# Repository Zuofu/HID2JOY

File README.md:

# HID2JOY
## Xbox One Controller (and other USB) to Analog IBM PC Gameport Adapter

### Intro
DOSBox has had the ability to map Xbox controllers to "Gameport" for a long time, but as far as I know, this is the first for people who want to use old hardware. I know of many converters that go the other way (use your old peripherals on a modern machine), but this allows you to use your nicer new controller with old machines. Anyway, this is WIP right now, and relies on Arduino, the USB Host Shield (MAX3421E) along with a Microchip DPot (actually, it's a rheostat). For now it only works with the Xbox One controller, since that's what the example code I started with is based off of, though it is trivial to extend to other supported controllers (Dualshock 3/4, Xbox 360..etc).

PCB is here: https://oshpark.com/projects/cPoLc5l8

### BOM:

1x Arduino Pro Mini or equivalent 3.3 V required - official or clones are fine, but make sure it's 3.3V

1x Mini USB Host Shield (based on MAX3421E) - find on eBay/Aliexpress/etc

1x MCP4452-104E digital rheostat (100K, quad channel, I2C)

2x 0603 4.7 kOhm resistor

1x 0603 .1uF ceramic capacitor

2x CES-112-01-T-S 12 position .1" pin header (low profile)

1x CES-102-02-T-S 2 position .1" pin header (low profile) or cut from larger part

1x ID15P33E4GV00LF or equivalent DB15 Male Connector right angle 2 row

Various .1" pin header strips

### Building and Modifications:

You should cut the trace on the USB Host Shield between 3.3V and VUSB, and then wire a jumper from RAW to VUSB. This will allow the controller to work with 5V (as per the USB spec) and also bypass the already overloaded regulator on the Arduino. Otherwise assemble the base PCB, then solder the Mini Host Shield with the Arduino into a stack and then solder the stack to the base PCB. Program the Arduino with the code as follows (you will need some USB serial port). If you get build errors, make sure you've installed the USB Host Shield 2.0 library using the Arduino Library manager. Make sure you connect also connected A6/A7 used for I2C (these are the two connections not in the parallel headers) between the Arduino and the PCB.

### Additional Usage Instructions (subject to change):
Holding down VIEW for 3 seconds switches modes. Here are the currently supported modes:

Standard 4 axis 4 button (mode 1)
Triggers and Buttons overloaded to A/B/X/Y

Thrustmaster emulation (mode 2)
Triggers are used for analog rudder X2 (Left/Right relative). Y2 is used for POV hat, multiple simultanous button presses are allowed. Note, I don't know the correct resistance values, can someone who owns Thrustmaster measure?

CH Flightstick emulation (mode 3)
Triggers are used for analog rudder X2 (Left/Right relative), left stick is used for digital POV hat along with D-pad. Buttons chords are used for POV hat (digital) . Multiple simultanous button pressed not allowed.

CH Flightstick emulation alternate (mode 4)
Triggers are used for analog rudder X2 (Left/Right relative), left stick is used for throttle (up/down). Buttons chords are used for POV hat (digital) with D-pad. Multiple simultanous button pressed not allowed.

Current design remembers last mode using EEPROM and will power up with last used mode.

Holding down MENU for 3 seconds swaps behavior of left and right sticks.

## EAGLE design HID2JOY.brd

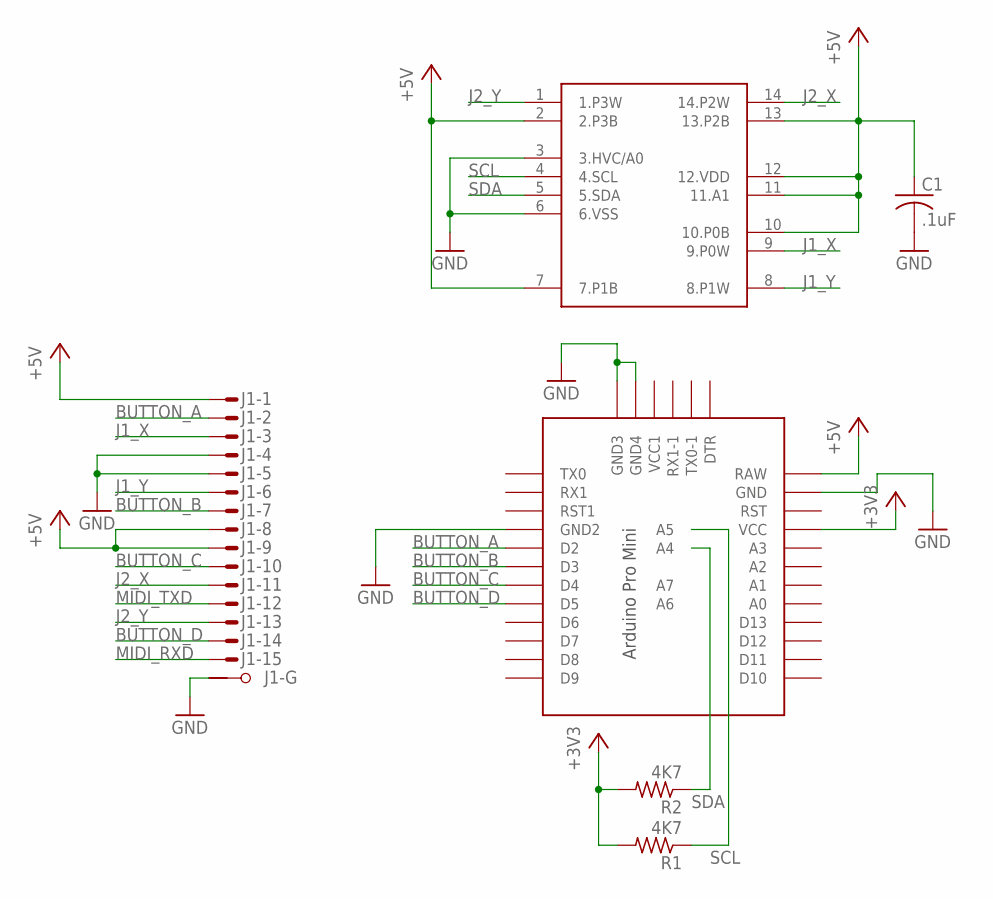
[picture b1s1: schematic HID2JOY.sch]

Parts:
C1: .1uF; C0603
J1: M15HPS; M15HP
R1, R2: 4K7; R0603
U1: PCM44X2TSSOP; TSSOP14
U$1: PRO-MINI-2

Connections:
+3V3: R1.2, R2.2, U$1.VCC
+5V: C1.1, J1.1 (M), J1.8 (M), J1.9 (M), U1.2 (2.P3B), U1.7 (7.P1B), U1.10 (10.P0B), U1.11 (11.A1), U1.12 (12.VDD), U1.13 (13.P2B), U$1.RAW
BUTTON_A: J1.2 (M), U$1.D2
BUTTON_B: J1.7 (M), U$1.D3
BUTTON_C: J1.10 (M), U$1.D4
BUTTON_D: J1.14 (M), U$1.D5
GND: C1.2, J1.4 (M), J1.5 (M), J1.G1, U1.3 (3.HVC/A0), U1.6 (6.VSS), U$1.GND, U$1.GND1 (GND2), U$1.GND2 (GND3), U$1.GND3 (GND4)
J1_X: J1.3 (M), U1.9 (9.P0W)
J1_Y: J1.6 (M), U1.8 (8.P1W)
J2_X: J1.11 (M), U1.14 (14.P2W)
J2_Y: J1.13 (M), U1.1 (1.P3W)
MIDI_RXD: J1.15 (M)
MIDI_TXD: J1.12 (M)
SCL: R1.1, U1.4 (4.SCL), U$1.A5
SDA: R2.1, U1.5 (5.SDA), U$1.A4

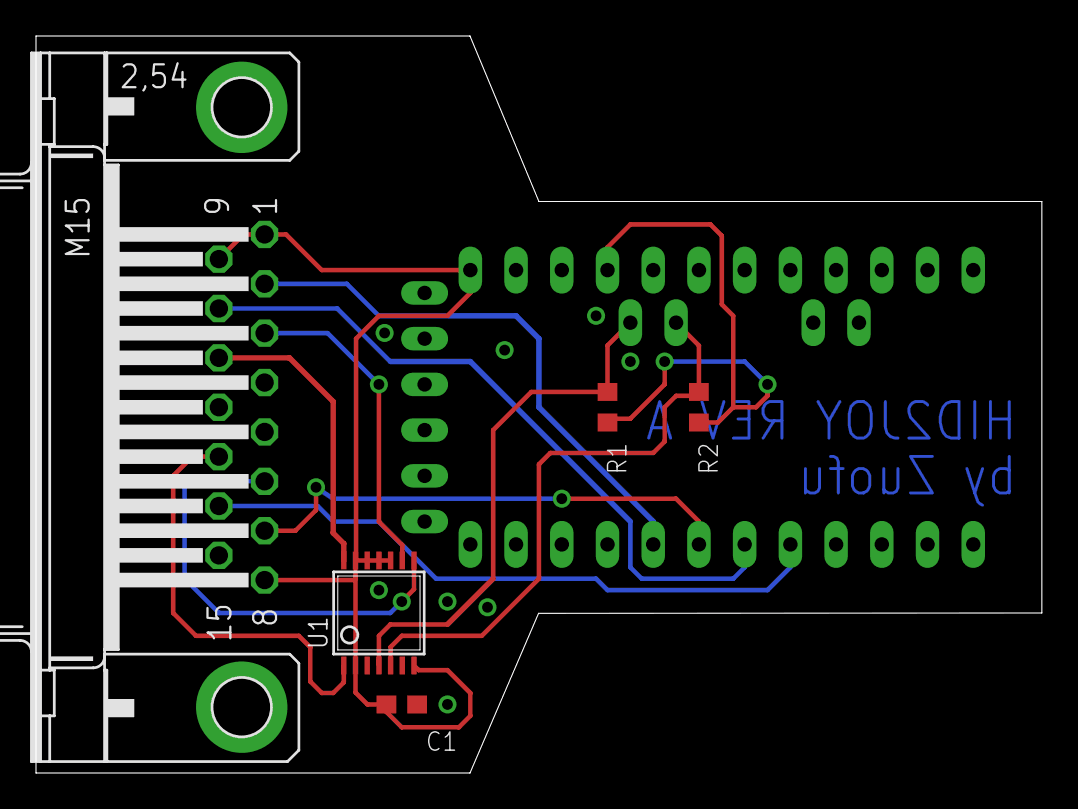
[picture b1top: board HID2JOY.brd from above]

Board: 2 copper layers, 55.9 x 40.9 mm, 6 parts (0 on the bottom side), 13 nets.

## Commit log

2022-06-20 Added CH Flightstick and Thrustmaster emulation modes. Thrustmaster mode isn't quite working in Strike Commander yet.
2022-06-21 Added images for mods and instructions.
2022-06-21 Modified Thrustmaster rudder behavior to be consistent with CH Flightstick. Also documented modes.
2022-06-21 Improved README.MD documentation
2022-06-21 I don't know how to use MD
2022-06-26 Added functionality to swap joysticks, also added CH Flightstick with second stick mapped to hat (useful for games which don't support analog throttle).
2022-07-02 Updated documentation.
